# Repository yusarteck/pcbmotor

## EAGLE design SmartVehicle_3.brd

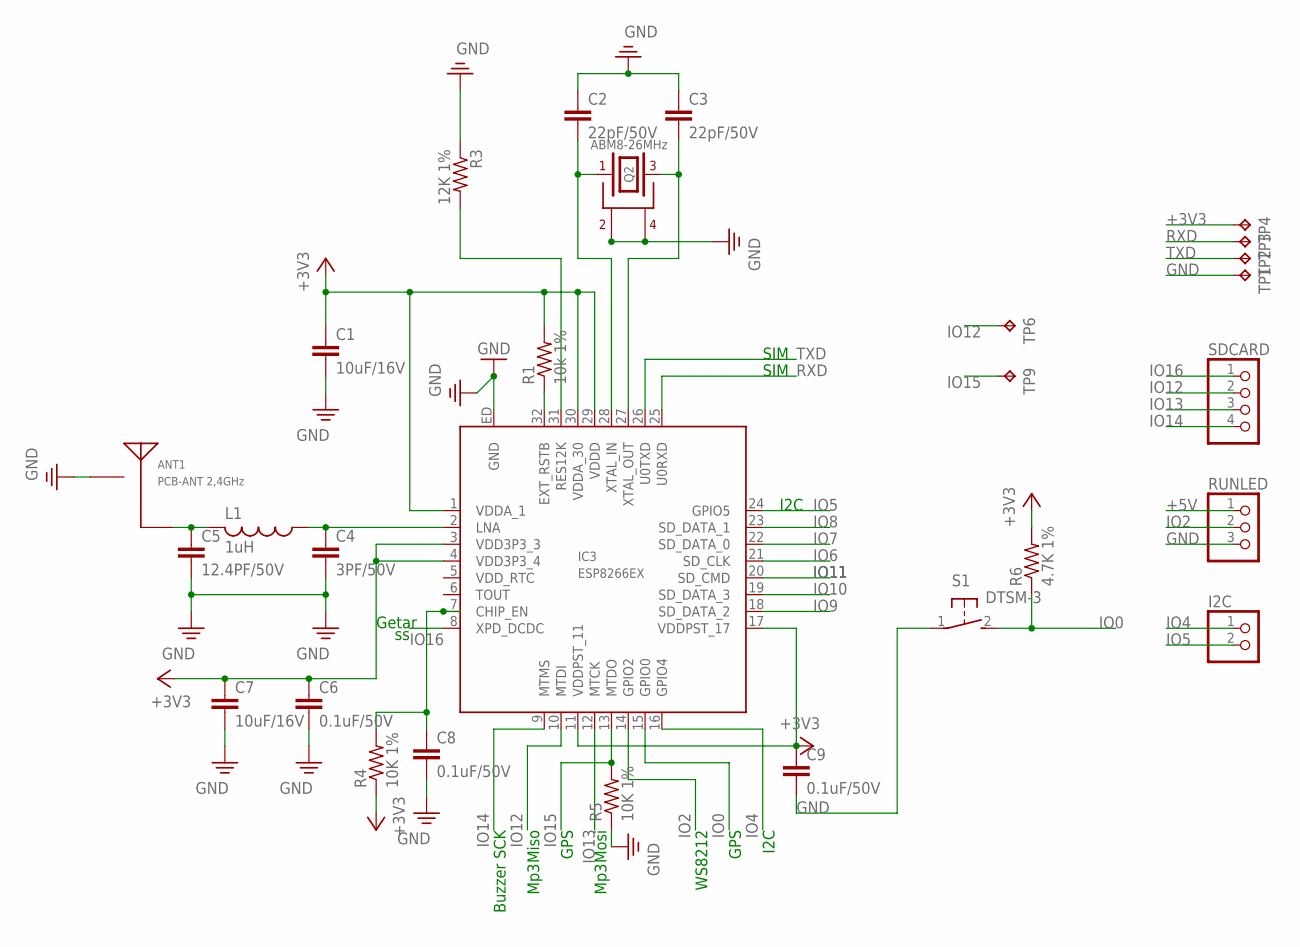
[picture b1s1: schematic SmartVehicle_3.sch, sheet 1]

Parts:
ANT1: PCB-ANT 2,4GHz; 2.4GHZ_PCB
C1, C7: 10uF/16V; C0603
C2, C3: 22pF/50V; C0603
C4: 3PF/50V; C0603
C5: 12.4PF/50V; C0603
C6, C8, C9: 0.1uF/50V; C0603
I2C: PINHD-1X2; 1X02
IC3: ESP8266EX
L1: 1uH; L2012C
Q2: ABM8-26MHz; ABM8G
R1: 10k 1%; R0603
R3: 12K 1%; R0603
R4, R5: 10K 1%; R0603
R6: 4.7K 1%; R0603
RUNLED: PINHD-1X3; 1X03
S1: DTSM-3
SDCARD: PINHD-1X4; 1X04
TP1, TP2, TP3, TP4, TP6, TP9: TPB1,27; B1,27

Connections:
+3V3: C1.1, C6.1, C7.1, C9.1, IC3.1 (VDDA_1), IC3.3 (VDD3P3_3), IC3.4 (VDD3P3_4), IC3.11 (VDDPST_11), IC3.17 (VDDPST_17), IC3.29 (VDDD), IC3.30 (VDDA_30), R1.2, R4.1, R6.2, TP4.TP; also elsewhere on the board
+5V: RUNLED.1; also elsewhere on the board
GND: ANT1.GND (2), C1.2, C2.1, C3.1, C4.2, C5.2, C6.2, C7.2, C8.2, C9.2, IC3.ED (GND), Q2.2, Q2.4, R3.1, R5.1, RUNLED.3, S1.1, TP1.TP; also elsewhere on the board
IO0: IC3.15 (GPIO0), R6.1, S1.2
IO2: IC3.14 (GPIO2), RUNLED.2
IO4: I2C.1, IC3.16 (GPIO4); also elsewhere on the board
IO5: I2C.2, IC3.24 (GPIO5); also elsewhere on the board
IO6: IC3.21 (SD_CLK)
IO7: IC3.22 (SD_DATA_0)
IO8: IC3.23 (SD_DATA_1)
IO9: IC3.18 (SD_DATA_2)
IO10: IC3.19 (SD_DATA_3)
IO11: IC3.20 (SD_CMD)
IO12: IC3.10 (MTDI), SDCARD.2, TP6.TP
IO13: IC3.12 (MTCK), SDCARD.3; also elsewhere on the board
IO14: IC3.9 (MTMS), SDCARD.4
IO15: IC3.13 (MTDO), R5.2, TP9.TP; also elsewhere on the board
IO16: IC3.8 (XPD_DCDC), SDCARD.1
unnamed: IC3.32 (EXT_RSTB), R1.1
unnamed: IC3.31 (RES12K), R3.2
unnamed: C2.2, IC3.28 (XTAL_IN), Q2.1
unnamed: C4.1, IC3.2 (LNA), L1.1
unnamed: C3.2, IC3.27 (XTAL_OUT), Q2.3
unnamed: ANT1.ANT (1), C5.1, L1.2
unnamed: C8.1, IC3.7 (CHIP_EN), R4.2
RXD: IC3.25 (U0RXD), TP3.TP; also elsewhere on the board
TXD: IC3.26 (U0TXD), TP2.TP; also elsewhere on the board

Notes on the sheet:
WS8212
GPS
I2C
SIM
Miso
SCK
Mosi
Mp3
Buzzer
Getar

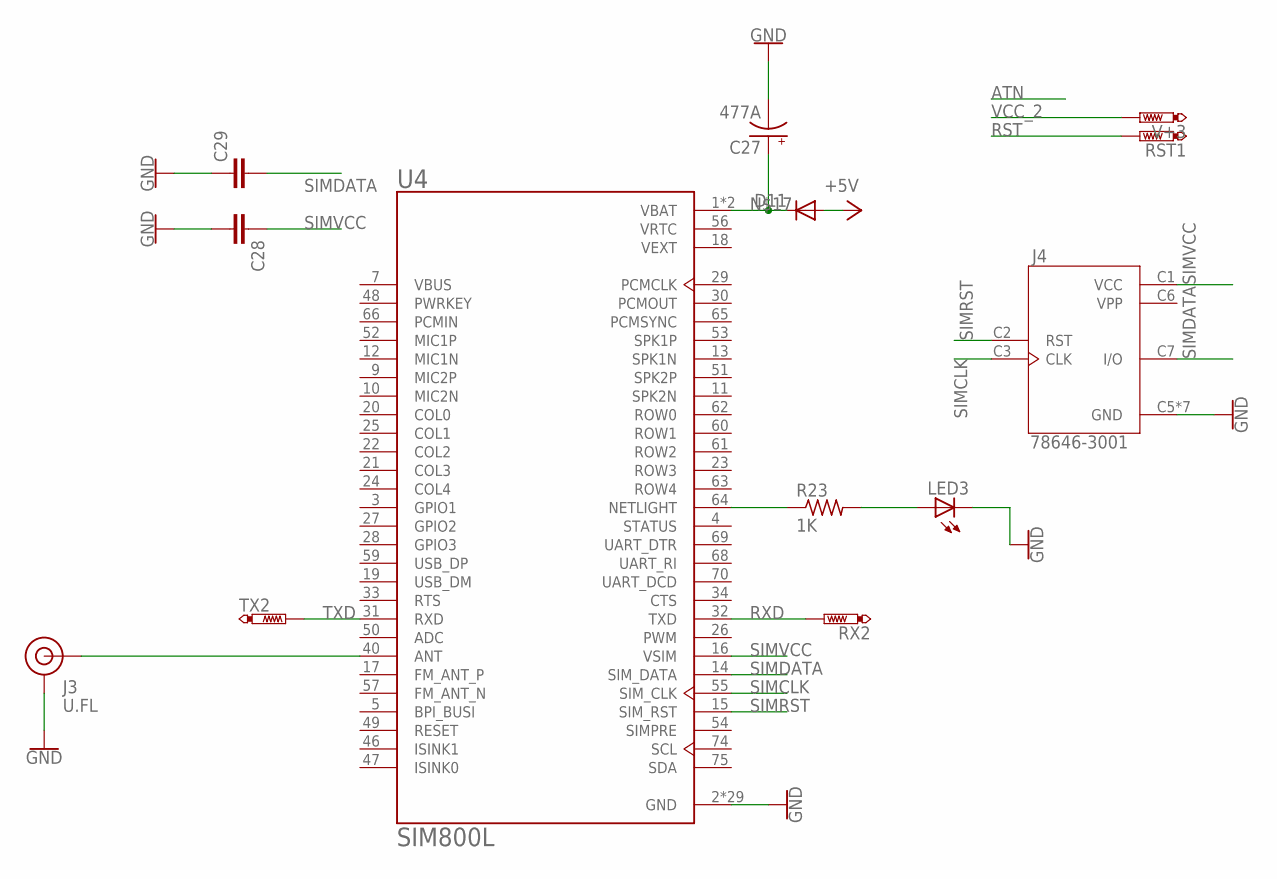
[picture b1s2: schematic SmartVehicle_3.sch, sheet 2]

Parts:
C27: 477A; CT7343
C28, C29: C-EUC0805; C0805
D11: DIODE-DO214AC; DO214AC
J3: U.FL
J4: 78646-3001; MOLEX_78646-3001
LED3: LEDCHIP-LED0805; CHIP-LED0805
R23: 1K; R0603
RST1: PTR1TP08R; TP08R
RX2: PTR1TP08R; TP08R
TX2: PTR1TP08R; TP08R
U4: SIM800L; MODULE_SIM800L
V+3: PTR1TP08R; TP08R

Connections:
+5V: D11.A; also elsewhere on the board
GND: C27.-, C28.2, C29.1, J3.1 (GND), J3.2 (GND), J4.C5 (GND), J4.G1 (GND), J4.G2 (GND), J4.G3 (GND), J4.G4 (GND), J4.G5 (GND), J4.G6 (GND), LED3.C, U4.2 (GND), U4.6 (GND), U4.8 (GND), U4.35 (GND), U4.37 (GND), U4.38 (GND), U4.39 (GND), U4.41 (GND), U4.43 (GND), U4.44 (GND), U4.45 (GND), U4.58 (GND), U4.67 (GND), U4.71 (GND), U4.72 (GND), U4.73 (GND), U4.76 (GND), U4.77 (GND), U4.78 (GND), U4.79 (GND), U4.80 (GND), U4.81 (GND), U4.82 (GND), U4.83 (GND), U4.84 (GND), U4.85 (GND), U4.86 (GND), U4.87 (GND), U4.88 (GND); also elsewhere on the board
unnamed: R23.1, U4.64 (NETLIGHT)
unnamed: C27.+, D11.C, U4.1 (VBAT), U4.42 (VBAT)
unnamed: LED3.A, R23.2
unnamed: J3.FEED (SIGNAL), U4.40 (ANT)
RST: RST1.TP
RXD: RX2.TP, U4.32 (TXD); also elsewhere on the board
SIMCLK: J4.C3 (CLK), U4.55 (SIM_CLK)
SIMDATA: C29.2, J4.C7 (I/O), U4.14 (SIM_DATA)
SIMRST: J4.C2 (RST), U4.15 (SIM_RST)
SIMVCC: C28.1, J4.C1 (VCC), U4.16 (VSIM)
TXD: TX2.TP, U4.31 (RXD); also elsewhere on the board
VCC_2: V+3.TP
VEXT: U4.18 (VEXT)
VPP: J4.C6 (VPP)
VRTC: U4.56 (VRTC)

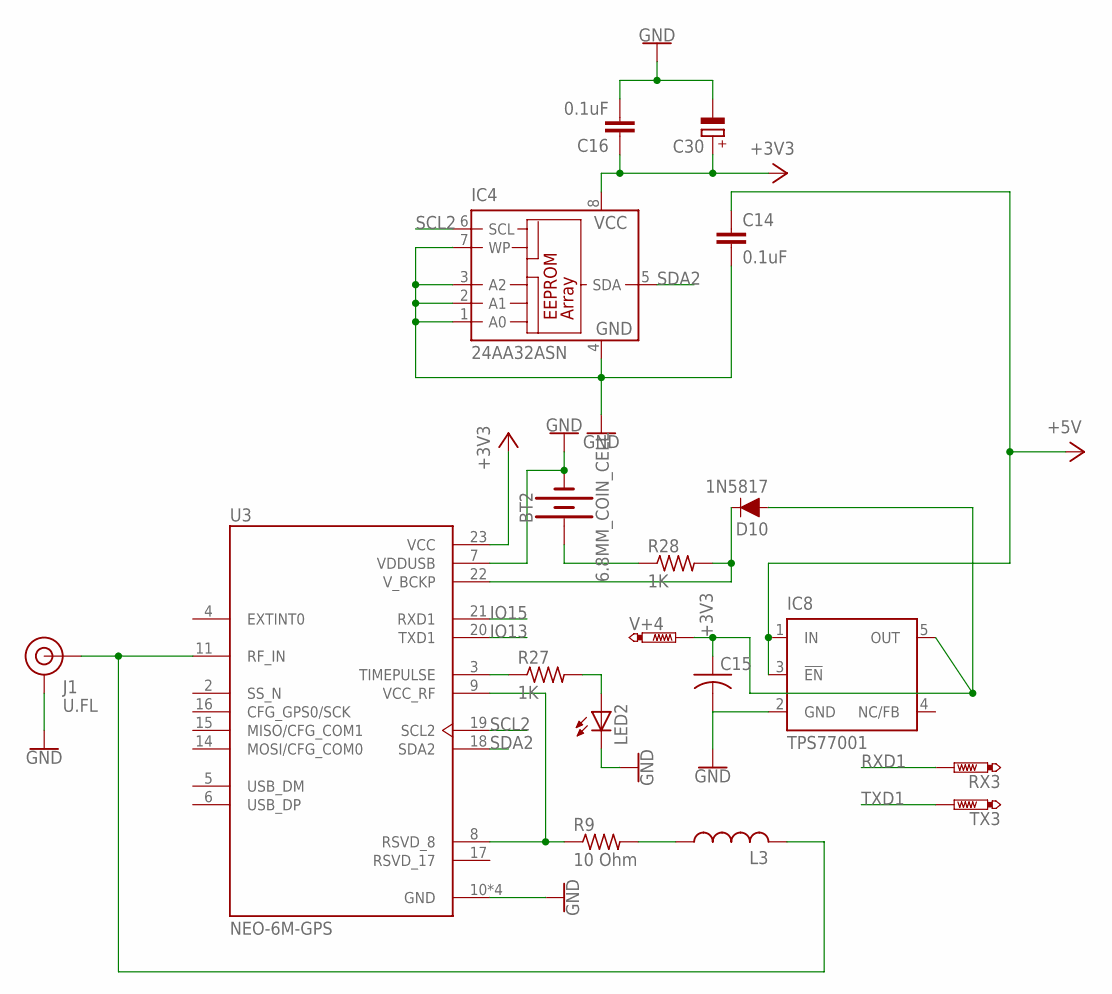
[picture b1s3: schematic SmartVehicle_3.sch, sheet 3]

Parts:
BT2: 6.8MM_COIN_CELL; BATTCON-6.8MM
C14, C16: 0.1uF; 0603
C15: C-USC0603K; C0603K
C30: CPOL-EUCT3528; CT3528
D10: 1N5817; SOD-323
IC4: 24AA32ASN; SO-08
IC8: TPS77001; SOT23-DBV
J1: U.FL
L3: L-USL2012C; L2012C
LED2: LEDCHIP-LED0805; CHIP-LED0805
R9: 10 Ohm; R0603
R27, R28: 1K; R0603
RX3: PTR1TP08R; TP08R
TX3: PTR1TP08R; TP08R
U3: NEO-6M-GPS; XCVR_NEO-6M-GPS
V+4: PTR1TP08R; TP08R

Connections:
+3V3: C15.1, C16.1, C30.+, D10.A, IC4.8 (VCC), IC8.5 (OUT), U3.23 (VCC), V+4.TP; also elsewhere on the board
+5V: C14.1, IC8.1 (IN), IC8.3 (!EN); also elsewhere on the board
GND: BT2.-, C14.2, C15.2, C16.2, C30.-, IC4.1 (A0), IC4.2 (A1), IC4.3 (A2), IC4.4 (GND), IC4.7 (WP), IC8.2 (GND), J1.1 (GND), J1.2 (GND), LED2.C, U3.7 (VDDUSB), U3.10 (GND), U3.12 (GND), U3.13 (GND), U3.24 (GND); also elsewhere on the board
IO13: U3.20 (TXD1); also elsewhere on the board
IO15: U3.21 (RXD1); also elsewhere on the board
unnamed: R27.1, U3.3 (TIMEPULSE)
unnamed: LED2.A, R27.2
unnamed: D10.C, R28.2, U3.22 (V_BCKP)
unnamed: R9.1, U3.8 (RSVD_8), U3.9 (VCC_RF)
unnamed: L3.1, R9.2
unnamed: BT2.+, R28.1
unnamed: J1.FEED (SIGNAL), L3.2, U3.11 (RF_IN)
RXD1: RX3.TP
SCL2: IC4.6 (SCL), U3.19 (SCL2)
SDA2: IC4.5 (SDA), U3.18 (SDA2)
TXD1: TX3.TP

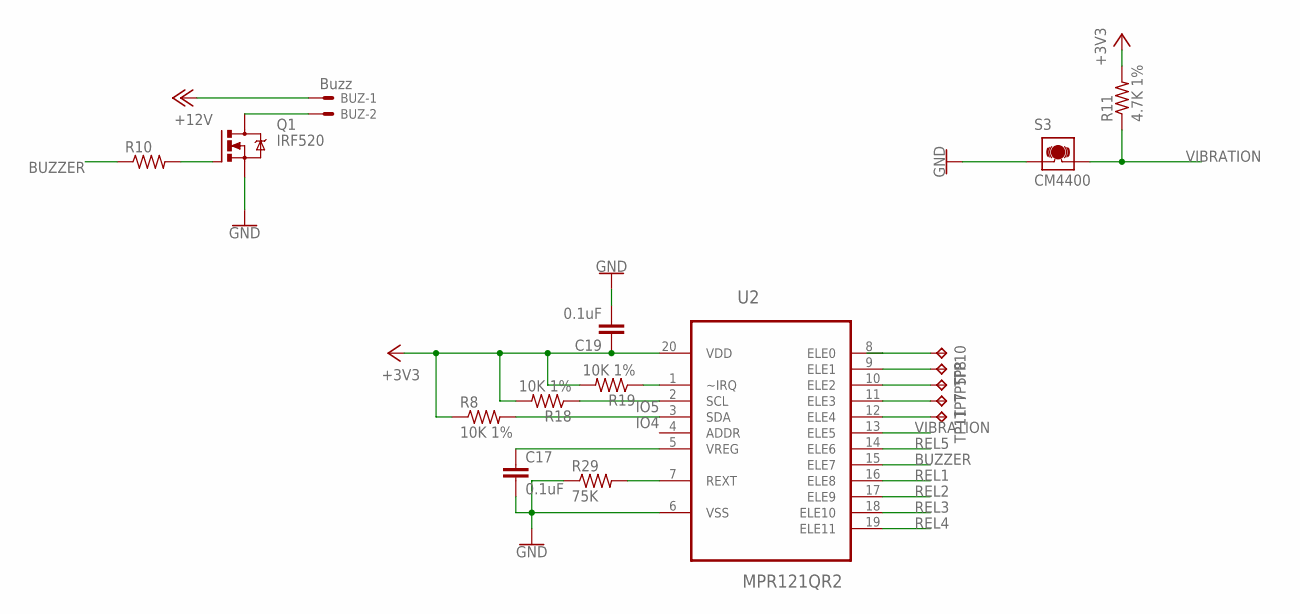
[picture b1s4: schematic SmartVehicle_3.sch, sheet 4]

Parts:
BUZ: Buzz; 22-23-2021
C17, C19: 0.1uF; C0603
Q1: IRF520; TO220BV
R8, R18, R19: 10K 1%; R0603
R10: R-US_R0603; R0603
R11: 4.7K 1%; R0603
R29: 75K; R0603
S3: CM4400
TP5, TP7, TP8, TP10, TP11: TPB1,27; B1,27
U2: MPR121QR2; QFN40P300X300X60-20N

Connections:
+3V3: C19.1, R8.1, R11.2, R18.2, R19.2, U2.20 (VDD); also elsewhere on the board
+12V: BUZ.1; also elsewhere on the board
BUZZER: R10.1, U2.15 (ELE7)
GND: C17.2, C19.2, Q1.S, R29.1, S3.1, U2.6 (VSS); also elsewhere on the board
IO4: R8.2, U2.3 (SDA); also elsewhere on the board
IO5: R18.1, U2.2 (SCL); also elsewhere on the board
unnamed: TP10.TP, U2.8 (ELE0)
unnamed: R19.1, U2.1 (~IRQ)
unnamed: R29.2, U2.7 (REXT)
unnamed: TP8.TP, U2.9 (ELE1)
unnamed: Q1.G, R10.2
unnamed: C17.1, U2.5 (VREG)
unnamed: TP11.TP, U2.12 (ELE4)
unnamed: BUZ.2, Q1.D
unnamed: TP5.TP, U2.10 (ELE2)
unnamed: TP7.TP, U2.11 (ELE3)
REL1: U2.16 (ELE8); also elsewhere on the board
REL2: U2.17 (ELE9); also elsewhere on the board
REL3: U2.18 (ELE10); also elsewhere on the board
REL4: U2.19 (ELE11); also elsewhere on the board
REL5: U2.14 (ELE6); also elsewhere on the board
VIBRATION: R11.1, S3.2, U2.13 (ELE5)

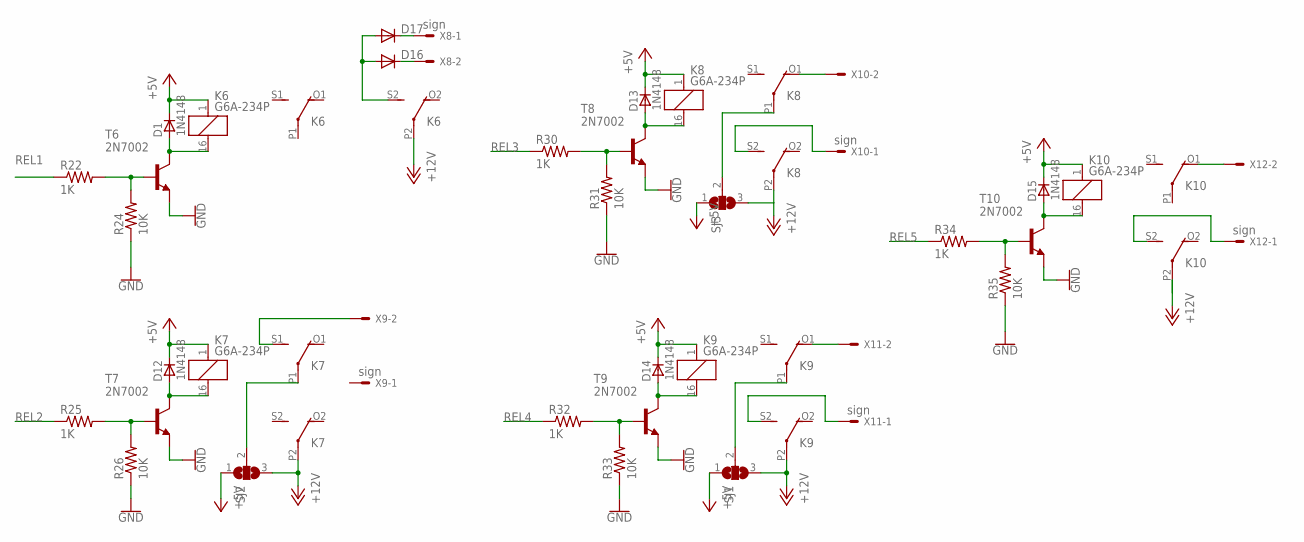
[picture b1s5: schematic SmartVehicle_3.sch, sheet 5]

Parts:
D1, D12, D13, D14, D15: 1N4148; SOD80_DO213AA_MINIMELF
D16, D17: DIODE-DO214AA; DO214AA
K6, K7, K8, K9, K10: G6A-234P
R22, R25, R30, R32, R34: 1K; M0805
R24, R26, R31, R33, R35: 10K; M0805
SJ1, SJ2, SJ3: SJ2W; SJ_2
T6, T7, T8, T9, T10: 2N7002; SOT23-BEC
X8, X9, X10, X11, X12: sign; 22-23-2021

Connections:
+5V: D1.C, D12.C, D13.C, D14.C, D15.C, K6.1, K7.1, K8.1, K9.1, K10.1, SJ1.1, SJ2.1, SJ3.1; also elsewhere on the board
+12V: K6.P2, K7.P2, K8.P2, K9.P2, K10.P2, SJ1.3, SJ2.3, SJ3.3; also elsewhere on the board
GND: R24.1, R26.1, R31.1, R33.1, R35.1, T6.E, T7.E, T8.E, T9.E, T10.E; also elsewhere on the board
unnamed: D16.A, D17.A, K6.S2 (S)
unnamed: K9.P1, SJ1.2
unnamed: D17.C, X8.1
unnamed: K8.P1, SJ3.2
unnamed: K7.P1, SJ2.2
unnamed: K7.S1 (S), X9.2
unnamed: D16.C, X8.2
unnamed: D1.A, K6.16 (2), T6.C
unnamed: R22.2, R24.2, T6.B
unnamed: D12.A, K7.16 (2), T7.C
unnamed: R25.2, R26.2, T7.B
unnamed: D13.A, K8.16 (2), T8.C
unnamed: R30.2, R31.2, T8.B
unnamed: K8.O1 (O), X10.2
unnamed: K8.S2 (S), X10.1
unnamed: D14.A, K9.16 (2), T9.C
unnamed: R32.2, R33.2, T9.B
unnamed: K9.O1 (O), X11.2
unnamed: K9.S2 (S), X11.1
unnamed: D15.A, K10.16 (2), T10.C
unnamed: R34.2, R35.2, T10.B
unnamed: K10.O1 (O), X12.2
unnamed: K10.S2 (S), X12.1
REL1: R22.1; also elsewhere on the board
REL2: R25.1; also elsewhere on the board
REL3: R30.1; also elsewhere on the board
REL4: R32.1; also elsewhere on the board
REL5: R34.1; also elsewhere on the board

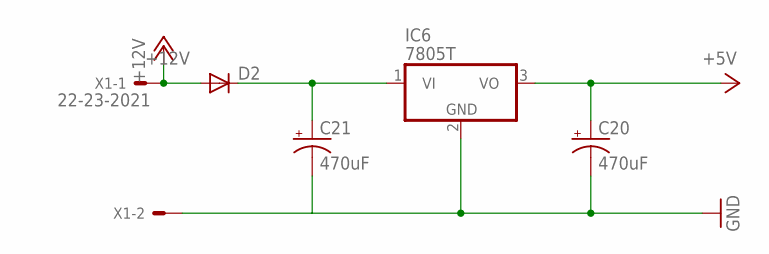
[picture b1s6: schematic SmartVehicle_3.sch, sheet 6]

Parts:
C20, C21: 470uF; E3,5-8
D2: DIODE-DO214AC; DO214AC
IC6: 7805T; TO220H
X1: 22-23-2021

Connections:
+5V: C20.+, IC6.3 (VO); also elsewhere on the board
+12V: D2.A, X1.1; also elsewhere on the board
GND: C20.-, C21.-, IC6.2 (GND), X1.2; also elsewhere on the board
unnamed: C21.+, D2.C, IC6.1 (VI)

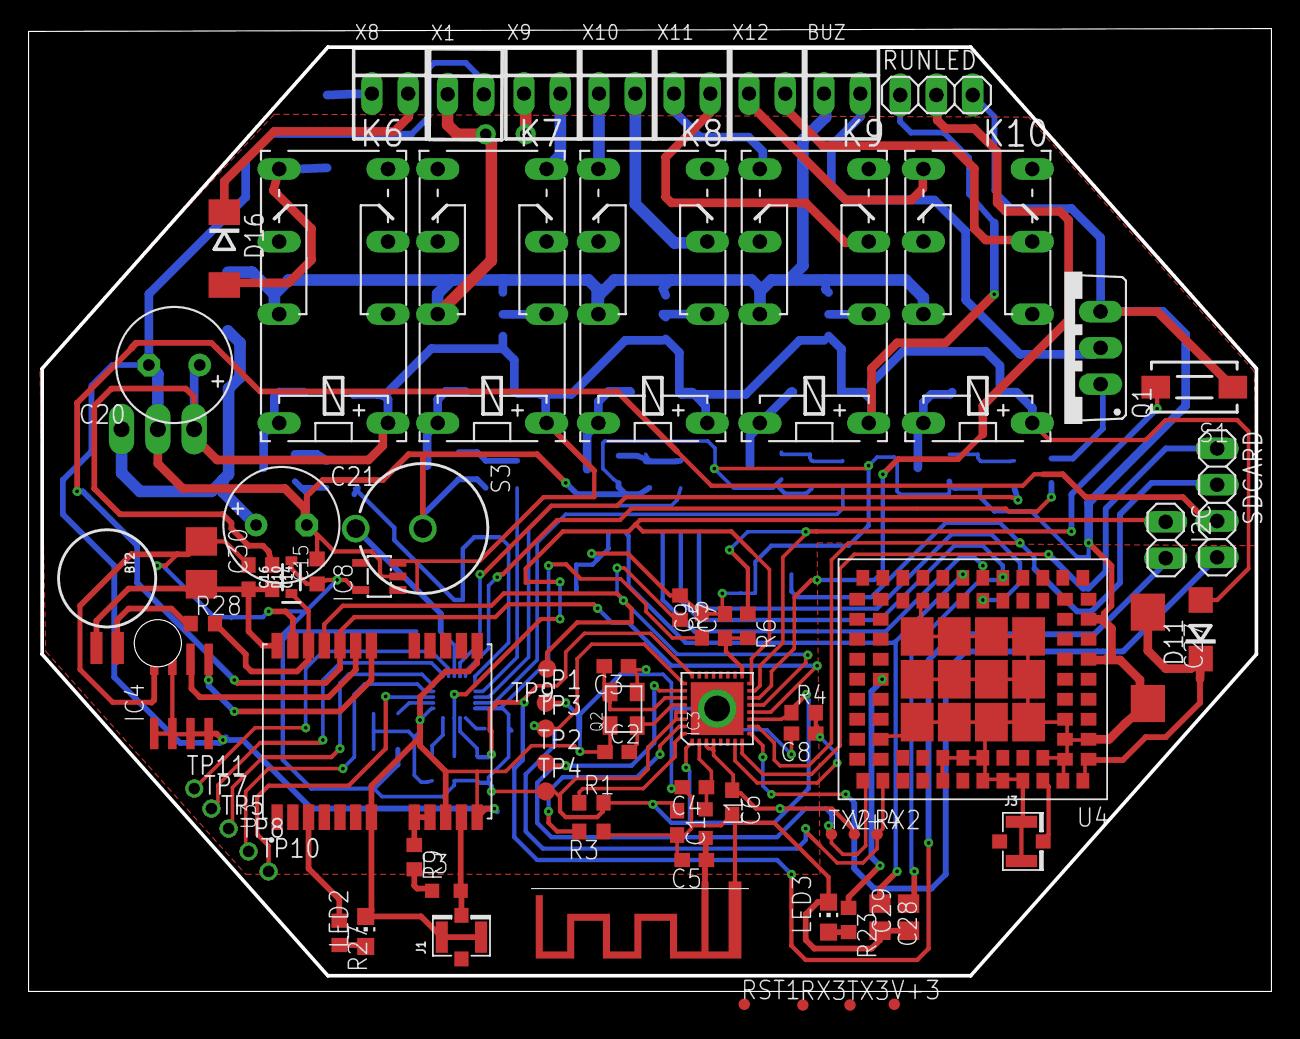
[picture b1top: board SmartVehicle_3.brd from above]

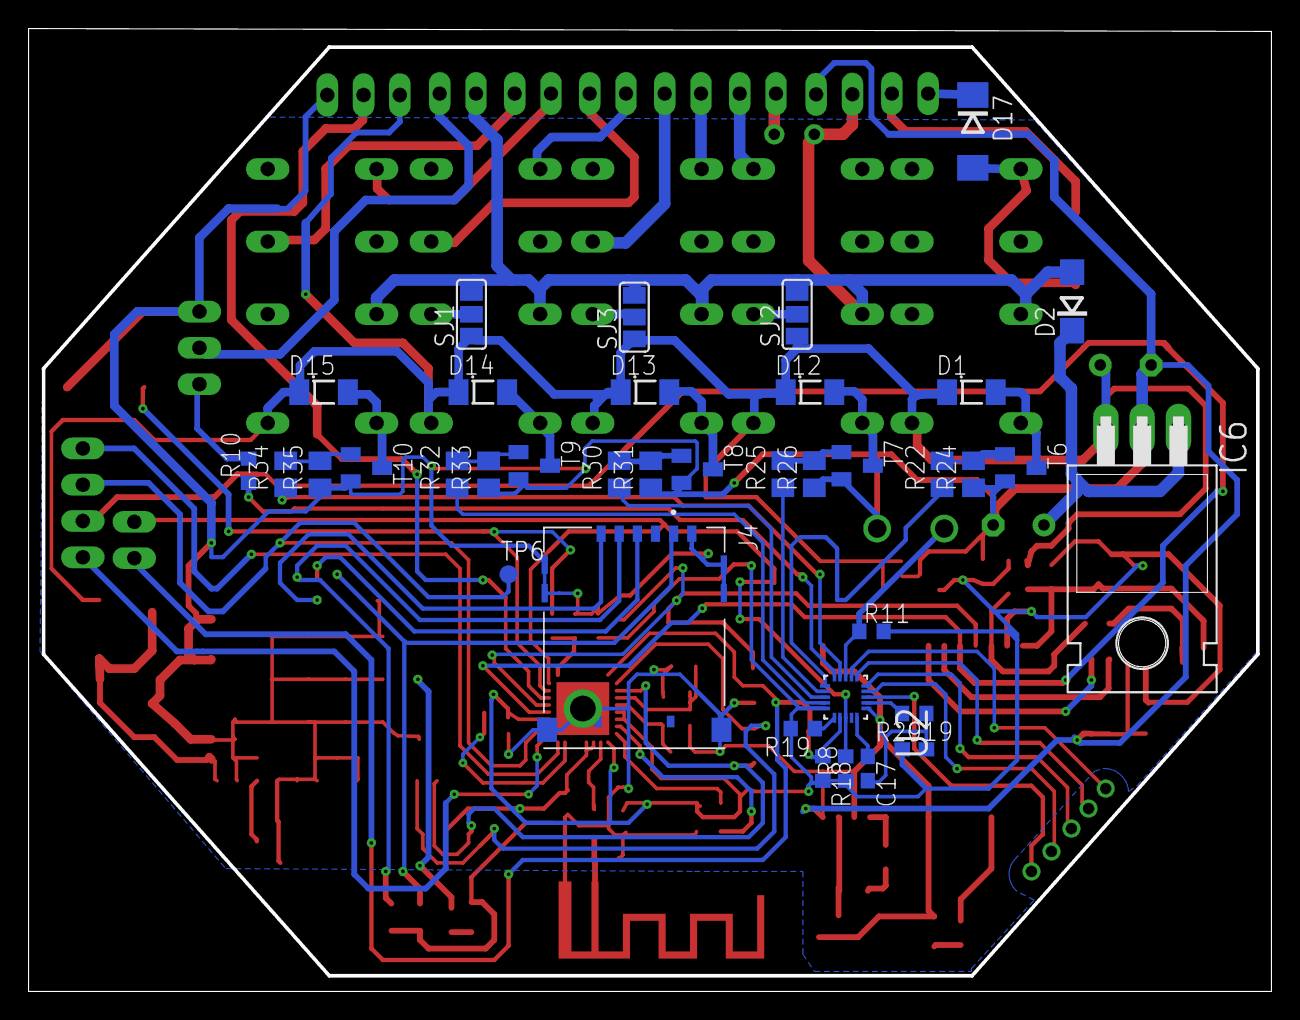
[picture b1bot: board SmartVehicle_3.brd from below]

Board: 2 copper layers, 86.7 x 67.1 mm, 116 parts (37 on the bottom side), 80 nets.

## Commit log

2020-02-05 commit pertama dari project sebelumnya
2020-02-05 update menambahkan Pin dang menghilangkan Gyro
2020-02-05 menambahkan via di pin
2020-02-05 menambahkan battery dan fix GPS
2020-02-07 merapihkan jalur yang berdempetan

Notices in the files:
parts and their libraries:
SparkFun-DiscreteSemi: Licensing: Creative Commons ShareAlike 4.0 International - https://creativecommons.org/licenses/by-sa/4.0
